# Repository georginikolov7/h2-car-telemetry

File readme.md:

# 🏎️ Hydrogen Racing Car Telemetry – Battery Monitoring

This project enables **real-time battery telemetry** for a **hydrogen-powered racing car**, built for high school competitions. It reads battery capacity using a Seeed XIAO nRF52 BLE board and transmits it via **Bluetooth Low Energy (BLE)** to a **.NET MAUI mobile app**.

> Please read this document carefully to understand the setup, components, and how to continue development.

---

## 📦 Contents

- 📁 `xiaoble-source/` – Firmware code for the Seeed XIAO board (C++ with PlatformIO)
- 📁 `pcb/` – KiCad files for the electrical design
- 📁 `maui-source/` – code for the mobile app (C# MAUI framework)
- 📄 `README.md` – Project documentation (you are here)

---

## ⚙️ System Overview

- **Board**: Seeed XIAO nRF52 BLE
- **Function**: Reads battery voltage/capacity and transmits data via BLE
- **Receiver**: Mobile app built with .NET MAUI
- **Firmware**: C++ using PlatformIO + Bluefruit library

---

## 🧰 Tools & Dependencies

### Hardware

- Seeed XIAO nRF52 BLE board
- Battery and voltage measuring circuit (see `pcb/`)
- Bluetooth-capable mobile device (Android)

### Parameters to keep in mind
Battery:
- Minimal voltage before cut-off - 6.4V
- Maximal charge voltage - 8.6V
---
!!! Since battery voltage range IS OUTSIDE working range of the seeed XIAO board, a voltage divider circuit is used to reduce the supplied voltage before passing it to analog input on the board !!!
---
### Software

- [PlatformIO](https://platformio.org/) (for microcontroller firmware)
- [KiCad](https://kicad.org/) (for circuit schematics)
- [.NET MAUI](https://learn.microsoft.com/en-us/dotnet/maui/) (for the mobile app)

---

## 📚 Used Libraries

### 🧠 Microcontroller (Seeed XIAO nRF52 BLE)

- **[Adafruit Bluefruit nRF52 Library](https://github.com/adafruit/Adafruit_nRF52_Arduino)**  
  Provides BLE support for nRF52 chips. Used to advertise services, send battery data, and manage BLE characteristics.

> No additional installation required

### 📱 Mobile App (MAUI)

- [Plugin.BLE](https://github.com/xabre/xamarin-bluetooth-le) by xabre  
  Cross-platform BLE plugin for Xamarin/.NET MAUI. Used to scan, connect, and read BLE data from the XIAO board.

Add via NuGet:

```bash
dotnet add package Plugin.BLE
```
---
## 🛠️ Getting Started

### Hardware 
- Please familiarize yourselves with the schematic design and used components (the power )

### 🚀 Firmware Setup (Microcontroller)

1. Install [Visual Studio Code](https://code.visualstudio.com/) with the [PlatformIO extension](https://platformio.org/install).
2. Open the project folder in VSCode.
3. Connect the Seeed XIAO nRF52 BLE board via USB.
4. Upload the firmware:

```bash
pio run --target upload
```
## 💡 Future Improvement Ideas

### 🧪 Add sensors for:

- Measure consumed current(use a ready-made board with low quiescent current. Ideally it should not rely on shunt resistors as such ones consume more power)  

- Hydrogen flow measurement

- Motor/controller temperature

- Wheel speed or RPM

### 📱 Improve the mobile app:

- Real-time graphs

- Database

## 🙏 Acknowledgments
Originally developed by Georgi Nikolov as part of the high school hydrogen racing program.
Now handed off to the next generation — good luck and keep innovating!

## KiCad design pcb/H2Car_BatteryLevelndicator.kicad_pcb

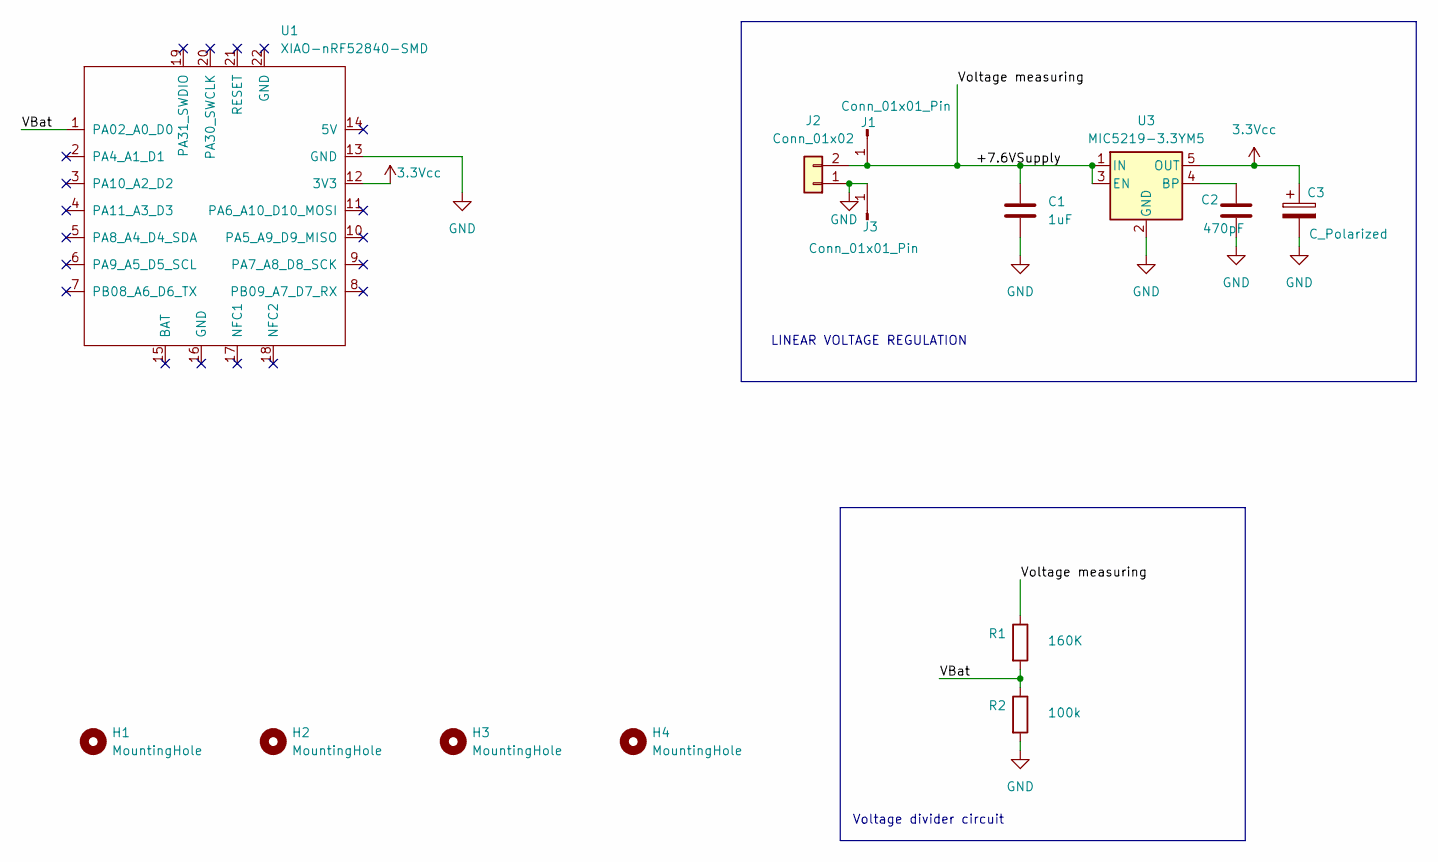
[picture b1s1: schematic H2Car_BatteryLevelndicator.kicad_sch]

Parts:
C1: 1uF; C_1206_3216Metric
C2: 470pF; C_0201_0603Metric
C3: C_Polarized; CP_EIA-3528-21_Kemet-B
H1, H2, H3, H4: MountingHole; MountingHole_2.2mm_M2_DIN965
J1, J3: Conn_01x01_Pin; SolderWire-0.75sqmm_1x01_D1.25mm_OD3.5mm
J2: Conn_01x02; JST_XH_S2B-XH-A_1x02_P2.50mm_Horizontal
R1: 160K; R_0805_2012Metric
R2: 100k; R_0805_2012Metric
U1: XIAO-nRF52840-SMD
U3: MIC5219-3.3YM5; SOT-23-5

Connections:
3.3Vcc: C3.1, U1.12 (3V3), U3.5 (OUT)
/+7.6VSupply: C1.1, J1.1, J2.2, R1.1, U3.1 (IN), U3.3 (EN)
/VBat: R1.2, R2.1, U1.1 (PA02_A0_D0)
GND: C1.2, C2.2, C3.2, J2.1, J3.1, R2.2, U1.13 (GND), U3.2 (GND)
unnamed: C2.1, U3.4 (BP)

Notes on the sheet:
Voltage divider circuit
LINEAR VOLTAGE REGULATION

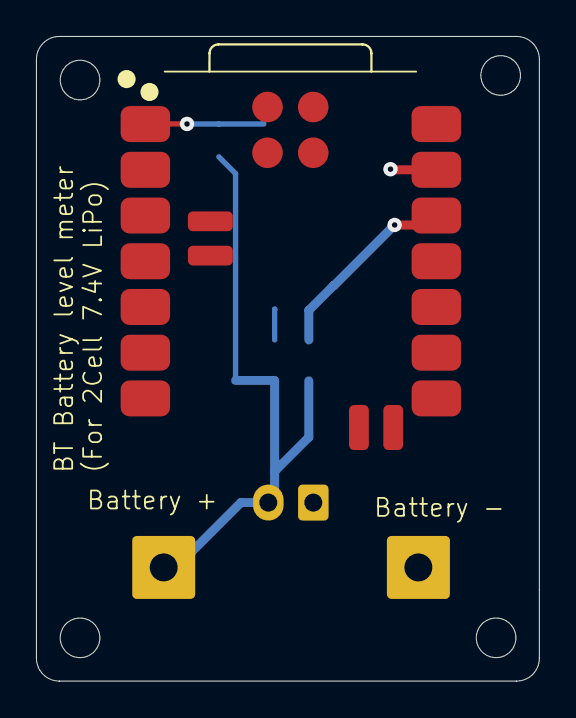
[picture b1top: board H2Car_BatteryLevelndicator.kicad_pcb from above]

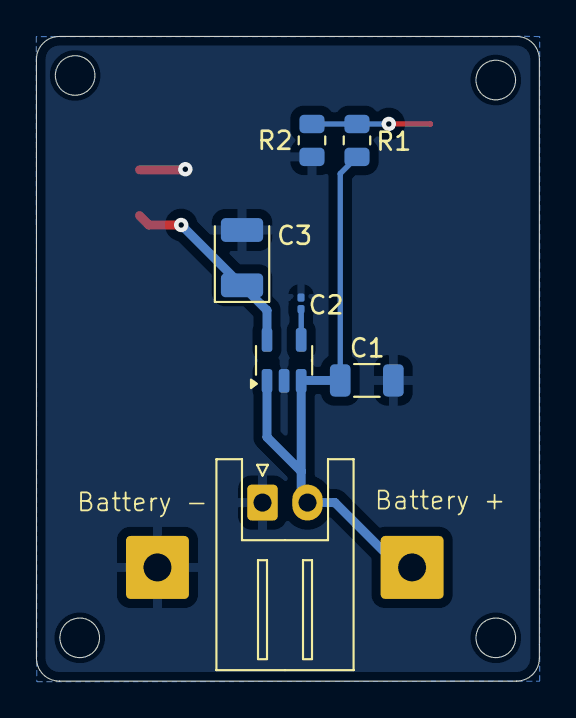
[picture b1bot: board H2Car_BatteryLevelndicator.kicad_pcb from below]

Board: 2 copper layers, 27.9 x 35.8 mm, 14 parts (7 on the bottom side), 5 nets.

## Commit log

2025-06-16 Init commit
2025-06-16 Added readme.md and renamed folders
2025-06-30 Include battery parameters in readme. Make schematic design more readable.
